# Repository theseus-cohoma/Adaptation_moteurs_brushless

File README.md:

# Adaptation_moteurs_brushless

Objectif du système (boucle de régulation) :

Le but est de piloter un moteur brushless via une carte ESC (Electronic Speed Controler) puis de récupérer la vitesse du moteur via des sondes à effet Hall grâce à un STM32.
Ce STM32 ainsi que l'ESC et le Jetson Nano seront connectés entre eux grâce au protocole de communication CAN.

L'ESC utilisé sera le B-G431B-ESC1 (https://www.st.com/en/evaluation-tools/b-g431b-esc1.html).

Une boite à été designée pour protéger l'ESC d'éventuels court-circuits.

[Partie basse de la boite](Modélisation_3D/box_part_bas.stl)
[Partie haute de la boite](Modélisation_3D/box_part_haut.stl)

Moteurs Brushless utilisés : BDUAV 6384-120KV SPECS (moteurs de skate électrique achetés sur Amazon, no name, très peu d'infos disponibles, pas de datasheet)

Adaptation transmission : 

L'enjeu était de pouvoir rempalacer les MCC par des Brushess. Il a donc fallut adapter la transmission. Pour cela nous avons modélisé deux disques qui venaient se fixer un sur le moteur Brushless et l'autre sur la gearbox. La liaison entre les deux tubes était effectuée par des tiges en métal sur les abords des diques et les deux axes de rotations de diamètres différents sont accouplés en utilisant un coupleur comme celui ci-dessous.

Les gearbox ont été usinés pour acceuillir 4 trous de fixation et les disques d'adaptation ont été imprimés en carbone.

Le système final qui tourne : 

https://github.com/user-attachments/assets/686f73e8-d420-4f12-8da8-5dcabd13b730

Le système une fois remonté dans l'habitacle du robot : 

https://github.com/user-attachments/assets/fa4666f8-0b14-431a-903d-8bc15e6b51ce

Détermination des caractéristiques techniques du moteur : 

Conception d'une carte de distribution de la puissance pour centraliser toute la partie puissance et éviter des brancehment en parallèle "sauvages":

Schématique : 

Routage :

PCB : 

La carte permet d'importer directement de la batterie et des transformateurs les 3 tensions du robot à savoir Vbatt, +12V et +8,4V via les 3 connecteurs XT60 sur la gauche.
Puis elle permet de redistribuer cette énergie via des connecteurs XT60 et des borniers avec le Vbatt sur la partie haute, le 12V au centre et le 8,4V sur le bas et le haut du PCB.
Il y a également de entrées PWM pour les Servos Moteurs.

Software (tuto) :

On lance d’abord motorControl Workbench > Load project là vous mettez le fichier BON_MOTEUR.stwb6 (dispo dans le dossier Fichier pour load les projects). Et ça vous ouvre directement la page(Image ci-dessous).

A gauche vous avez les paramètres que vous pouvez modifier etc. Pour lancer motor Pilot il faut Generate the Project :

Cliquer sur generate ça le genére (si vous voyez des lignes orange pas d’inquiétude). Une fois la génération finit,il vous suffit d’appuyer sur Run STM32CubeMx.
A ce stade normalement, unpage STM32CubeMx se lance appuyer sur Generate the code. Ensuite, appuyer sur ouvrez un fichier c de la barre à gaucheet appuyez sur RUN.
Pendant ce temps vous pouvez lancer motorpilot via motor Control workbench (bouton à coter de
Generate the project).
Remarque, l’application qui se lancera va dépendre de ce que vous avez cocher dans Application
Configuration.

Dans tous les cas, ceci est la page de base:

Vous pouvez aussi tout contrôler en haut à gauche avec GUI. Enfin, si vous choisissez Load UI il faut choisir le fichier MC_FOC_SDK pour avoir l’interface suivante et contrôler le moteur:

Dans l’onglet Control vous pouvez choisir de le contrôler en Torque ou en Speed. Si jamais vous avez un problème de over current, il faut régler le problème ici :

Dans Digital Filter Duration, il faut augmenter le temps ici j’ai mis 282.35 ns.

REMARQUE IMPORTANTE : IL FAUT à CHAQUE FOIS RE-GENERATE the project > Run
STM32CubeMx > Generate the code > Run un fichier C POUR CHAQUE CHANGEMENT QUE
VOUS FAITES DANS LE SOFTWARE MC WORKBENCH. (En tout cas c’est la seule façon avec
laquelle on arrivait à faire en sorte que les changements dans le software soit pris en compte si
jamais vous trouvez une autre méthode plus court, bien joué).

J’ai fournit les fichier JSON obtenu via MOTOR Profiler( dans le dossier Fichier pour load les
projects, vous remarquerez qu’il y en a deux, celui « Moteur présentation » c’est le fichier que l’on
a utiliser pour la présentation de S7, et l’autre c’est celui qu’on a utilisé pour les applications
présentées plus hauts). Libre à vous de tester et d’observer les mesures. Ce software permet
d’identifier les « composants » et leurs valeurs du moteur et faute de datasheet sur les moteurs
commandées, on a du faire avec les moyens du bord.

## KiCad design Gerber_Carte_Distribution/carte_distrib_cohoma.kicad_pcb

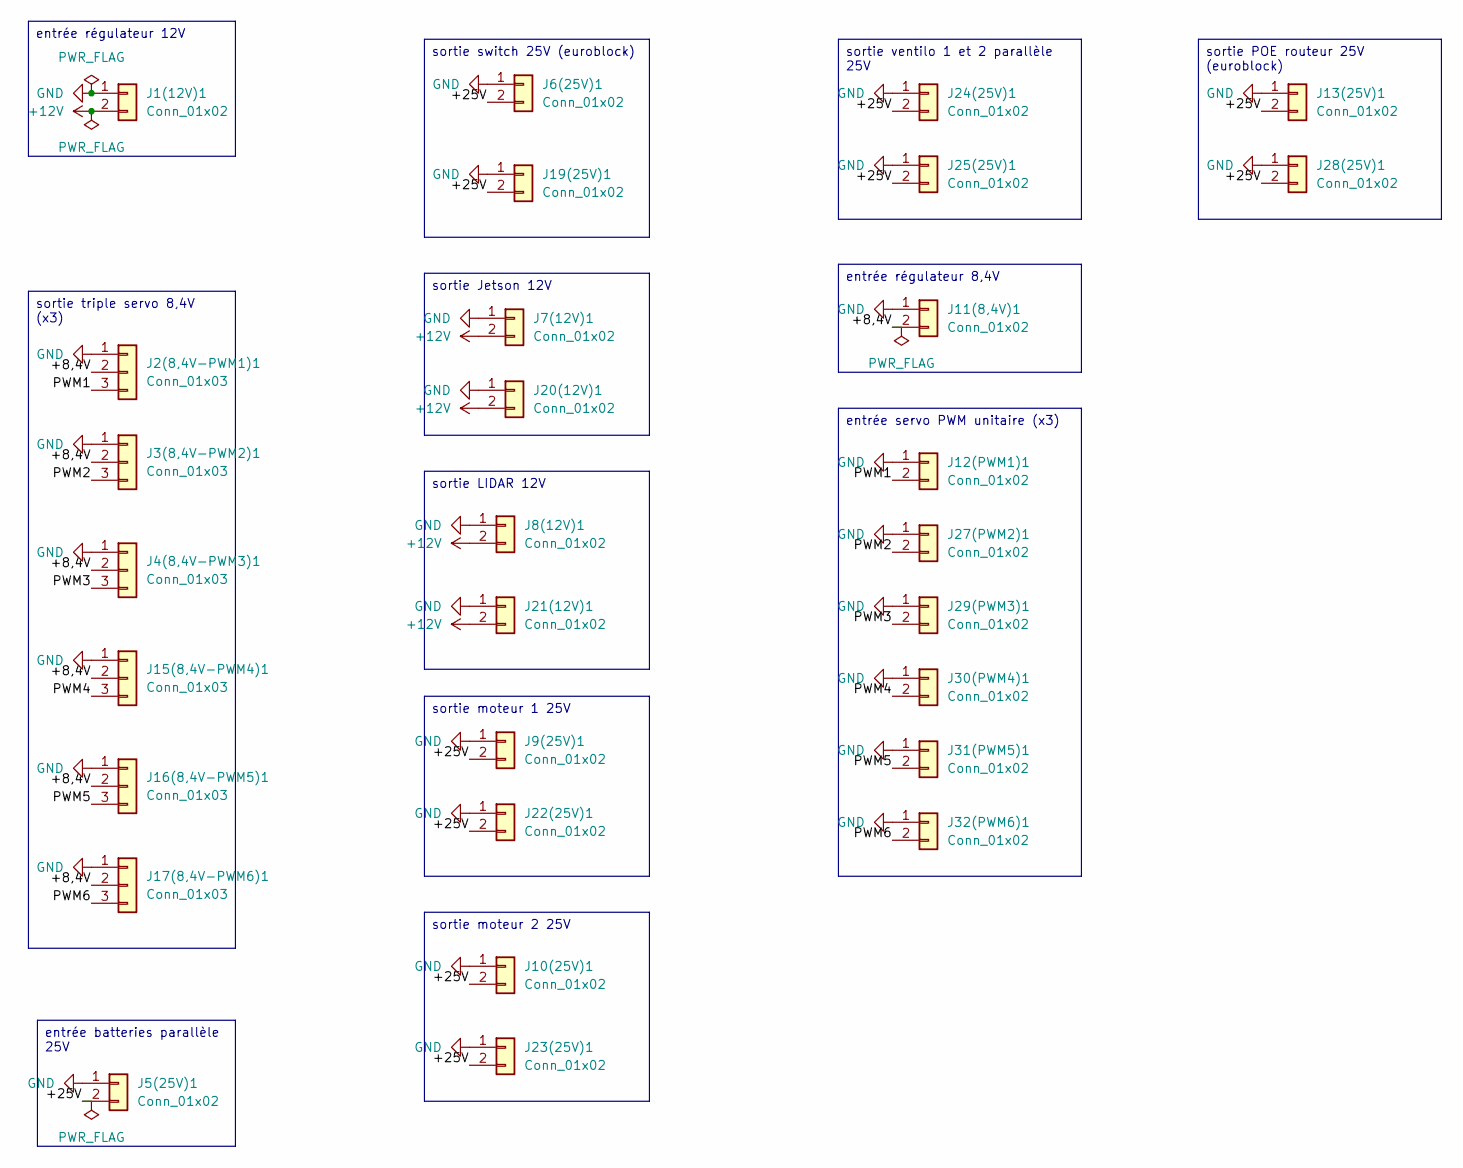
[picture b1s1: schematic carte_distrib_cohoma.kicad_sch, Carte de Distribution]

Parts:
J1(12V)1, J5(25V)1, J11(8,4V)1: Conn_01x02; AMASS_XT60-M_1x02_P7.20mm_Vertical
J2(8,4V-PWM1)1, J3(8,4V-PWM2)1, J4(8,4V-PWM3)1, J15(8,4V-PWM4)1, J16(8,4V-PWM5)1, J17(8,4V-PWM6)1: Conn_01x03; CONN3_KF301-3P - BLACK_CKE
J6(25V)1, J8(12V)1, J20(12V)1, J22(25V)1, J23(25V)1, J25(25V)1, J28(25V)1: Conn_01x02; HANDSON_KF301-2P
J7(12V)1, J9(25V)1, J10(25V)1, J13(25V)1, J19(25V)1, J21(12V)1, J24(25V)1: Conn_01x02; AMASS_XT60-F_1x02_P7.20mm_Vertical
J12(PWM1)1, J27(PWM2)1, J29(PWM3)1, J30(PWM4)1, J31(PWM5)1, J32(PWM6)1: Conn_01x02; JST_PH_B2B-PH-K_1x02_P2.00mm_Vertical

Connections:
+12V: J1(12V)1.2, J7(12V)1.2, J8(12V)1.2, J20(12V)1.2, J21(12V)1.2
/+8,4V: J2(8,4V-PWM1)1.2, J3(8,4V-PWM2)1.2, J4(8,4V-PWM3)1.2, J11(8,4V)1.2, J15(8,4V-PWM4)1.2, J16(8,4V-PWM5)1.2, J17(8,4V-PWM6)1.2
/+25V: J5(25V)1.2, J6(25V)1.2, J9(25V)1.2, J10(25V)1.2, J13(25V)1.2, J19(25V)1.2, J22(25V)1.2, J23(25V)1.2, J24(25V)1.2, J25(25V)1.2, J28(25V)1.2
/PWM1: J2(8,4V-PWM1)1.3, J12(PWM1)1.2
/PWM2: J3(8,4V-PWM2)1.3, J27(PWM2)1.2
/PWM3: J4(8,4V-PWM3)1.3, J29(PWM3)1.2
/PWM4: J15(8,4V-PWM4)1.3, J30(PWM4)1.2
/PWM5: J16(8,4V-PWM5)1.3, J31(PWM5)1.2
/PWM6: J17(8,4V-PWM6)1.3, J32(PWM6)1.2
GND: J1(12V)1.1, J2(8,4V-PWM1)1.1, J3(8,4V-PWM2)1.1, J4(8,4V-PWM3)1.1, J5(25V)1.1, J6(25V)1.1, J7(12V)1.1, J8(12V)1.1, J9(25V)1.1, J10(25V)1.1, J11(8,4V)1.1, J12(PWM1)1.1, J13(25V)1.1, J15(8,4V-PWM4)1.1, J16(8,4V-PWM5)1.1, J17(8,4V-PWM6)1.1, J19(25V)1.1, J20(12V)1.1, J21(12V)1.1, J22(25V)1.1, J23(25V)1.1, J24(25V)1.1, J25(25V)1.1, J27(PWM2)1.1, J28(25V)1.1, J29(PWM3)1.1, J30(PWM4)1.1, J31(PWM5)1.1, J32(PWM6)1.1

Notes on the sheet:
entrée batteries parallèle 25V
sortie moteur 1 25V
sortie moteur 2 25V
sortie ventilo 1 et 2 parallèle 25V
sortie POE routeur 25V (euroblock)
sortie Jetson 12V
sortie switch 25V (euroblock)
sortie triple servo 8,4V (x3)
sortie LIDAR 12V
entrée régulateur 12V
entrée régulateur 8,4V
entrée servo PWM unitaire (x3)

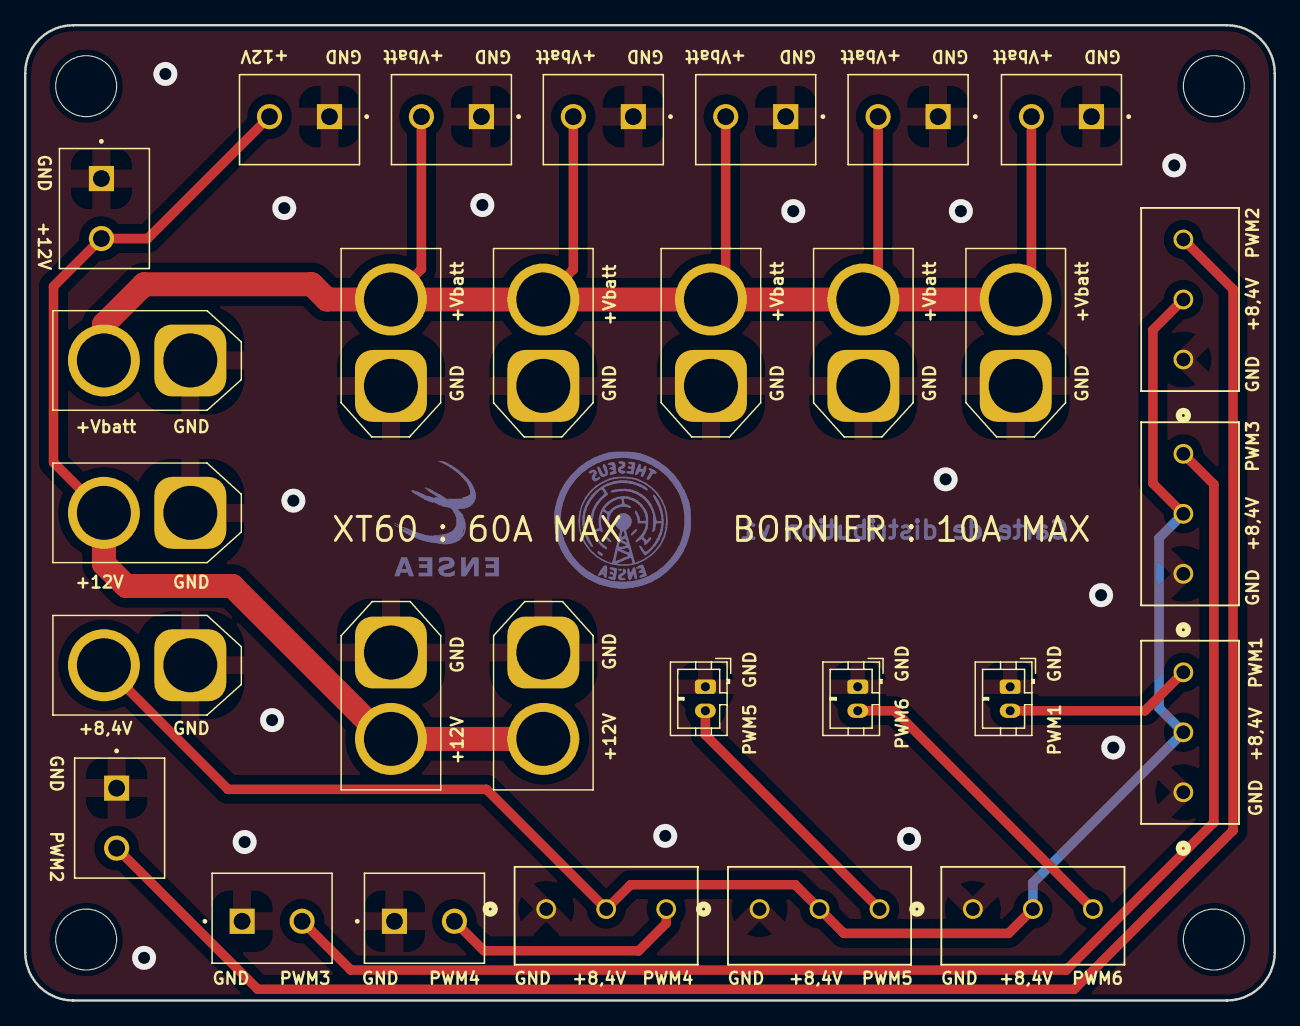
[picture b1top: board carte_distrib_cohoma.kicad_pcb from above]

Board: 2 copper layers, 104.1 x 81.3 mm, 29 parts (0 on the bottom side), 10 nets.

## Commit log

2026-04-10 Rename box - Part haut.stl to box_part_haut.stl
2026-04-10 Rename box - Part bas.stl to box_part_bas.stl
2026-04-10 carte_distrib
2026-04-23 Ajout fichiers
2026-04-25 Ajout des dossiers et fichiers du software pour les futures 2A
2026-04-25 Update README with clearer instructions and file details
    Clarified instructions and added details about JSON files in the README.
